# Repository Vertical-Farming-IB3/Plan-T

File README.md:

# Plan-T 🌱  

Plan-T is een vertical farming (VF) project met hydroponics, gericht op het duurzaam kweken van kruiden en groenten. De VF-installatie wordt grotendeels automatisch bestuurd en gemonitord, met ruimte voor menselijke input waar nodig — zoals bij controle, onderhoud en oogst (een vorm van mens-in-de-lus automatisering).

## Voor meer info:  
- [Team Plantenbak](./Plantenbak)  
- [Team Water](./Water)  
- [Team Licht](./Licht)
- [Team Power](./Power)  

Bezoek onze [website](https://vertical-farming-ib3.github.io/),
en zijn [repository](https://github.com/Vertical-Farming-IB3/vertical-farming-ib3.github.io/tree/main).

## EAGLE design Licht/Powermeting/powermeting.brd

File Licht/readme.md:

Het team bestaat uit:
- Daan Vercammen
- Andres Bosman
- Syme Vandenbosch
- Arne Van der Stede
- Cas Truyers
- Stijn Verhaeghe

Meer info [hier](https://vertical-farming-ib3.github.io/Licht/).

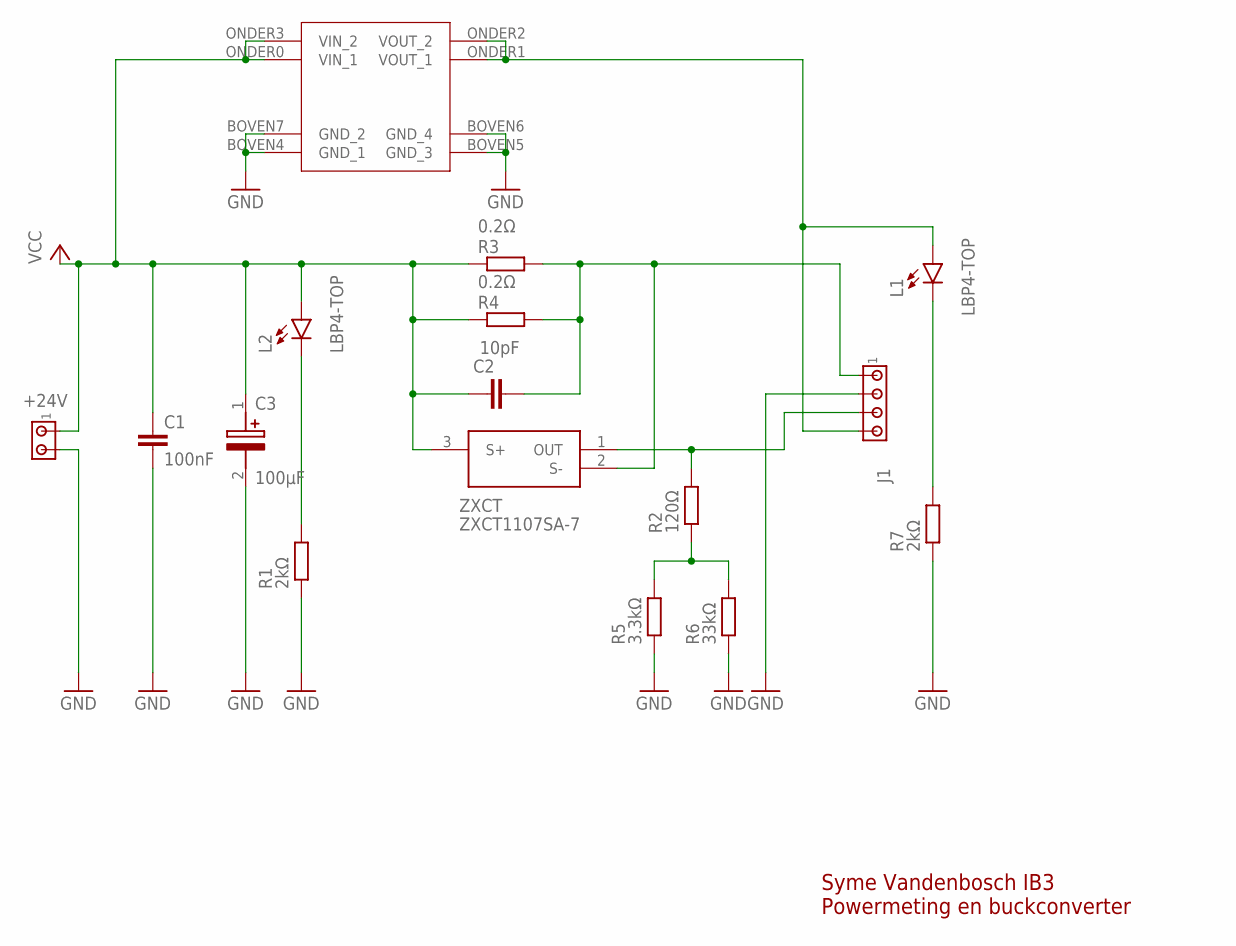
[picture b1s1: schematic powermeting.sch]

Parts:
+24V: MTA02-100; 10X02MTA
C1: 100nF; C0805K
C2: 10pF; C0805K
C3: 100µF; EEHZA1H100R
J1: MTA04-100; 10X04MTA
L1, L2: LBP4-TOP; LED3MM
R1, R7: 2kΩ; M0805
R2: 120Ω; M0805
R3, R4: 0.2Ω; M1206
R5: 3.3kΩ; M0805
R6: 33kΩ; M0805
U$1: BUCK
ZXCT: ZXCT1107SA-7; SOT96P240X110-3N

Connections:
GND: +24V.2, C1.2, C3.2 (-), J1.2, R1.1, R5.1, R6.1, R7.1, U$1.BOVEN4 (GND_1), U$1.BOVEN5 (GND_3), U$1.BOVEN6 (GND_4), U$1.BOVEN7 (GND_2)
unnamed: L1.K (C), R7.2
unnamed: L2.K (C), R1.2
unnamed: R2.1, R5.2, R6.2
unnamed: C2.2, J1.1, R3.1, R4.1, ZXCT.2 (S-)
unnamed: J1.4, L1.A, U$1.ONDER1 (VOUT_1), U$1.ONDER2 (VOUT_2)
unnamed: J1.3, R2.2, ZXCT.1 (OUT)
VCC: +24V.1, C1.1, C2.1, C3.1 (+), L2.A, R3.2, R4.2, U$1.ONDER0 (VIN_1), U$1.ONDER3 (VIN_2), ZXCT.3 (S+)

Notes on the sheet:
Syme Vandenbosch IB3 Powermeting en buckconverter

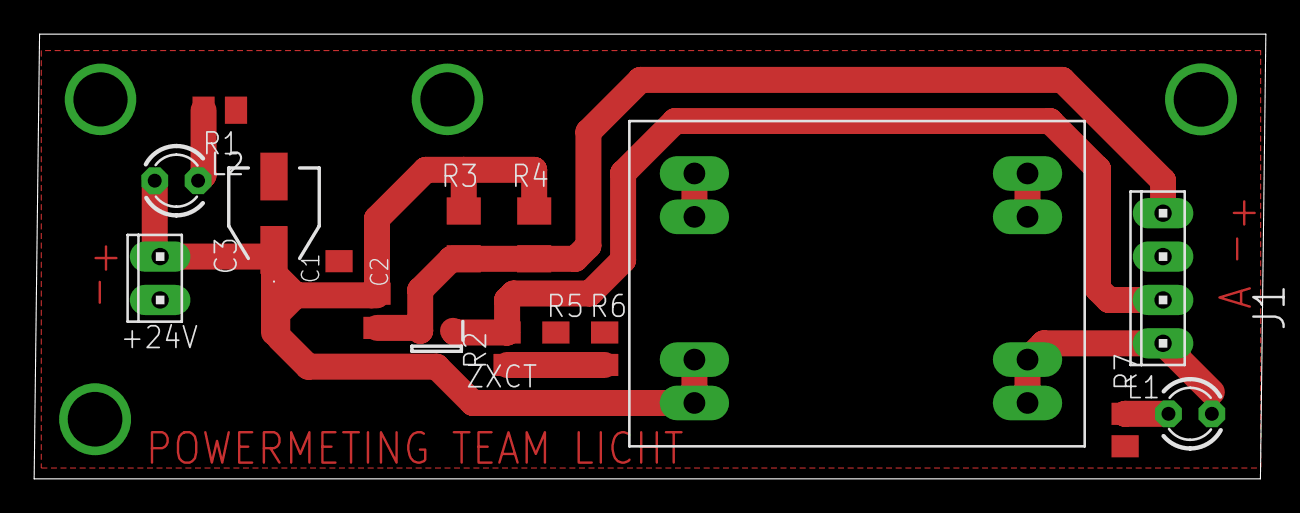
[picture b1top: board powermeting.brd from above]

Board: 2 copper layers, 72.1 x 26.0 mm, 16 parts (0 on the bottom side), 8 nets.

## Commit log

2024-10-16 Brainstorming Session October 16
2024-10-22 added log of 22/10
2024-10-22 Added documentation folder
    Added a doc folder with information about the project done in 2023-2024, specifically the connection of the source to the vertical farm.
2024-12-20 Onderverdeling mappen + markdown watersysteem
    Folders toegevoegd per huidig gekend team + in watersysteem een markdown voorzien met informatie over het watersysteem
2025-01-27 Added 3D-models
    Added 3D-models and assemblies of the water system and common connector (both still WIP)
2025-02-05 Add files via upload
    Enkele opzoekingen. Keuze welke bestellen na controle.
2025-02-06 Log update after presentation
2025-02-06 Overzicht van onderdelen
2025-02-06 UV filter
2025-02-11 Word document samengevoegd met markdown
    Alle informatie uit het word document is in het markdown document geplaatst
2025-02-11 Create test
2025-02-11 Wijzigingen na bespreking
2025-02-11 Update na bespreking
2025-02-17 aanpassing naar keukenmodel
2025-02-18 Update 3D modellen
    Plantenbakken herwerkt (randen weggevijld zodat ze onderaan passen) + Buitenste 'shell' van kast
2025-02-18 PCB requirements input/output
2025-02-18 Ruwe berekening vermogen
2025-02-18 Add files via upload
    Gantt Chart
2025-02-19 PCB Watersysteem initial commit
    Ontwerp PCB initial commit: deel van schema van PCB, custom symbol + footprints (MP1584 buck converter module), symbol+footprint van 5V relais
2025-02-23 Update PCB watersysteem
2025-02-24 PCB update
    ADC verbonden, LED outputs, Eindeloops, Voorbeeld relais
2025-02-24 Moved to correct folder
2025-02-25 Add files via upload
    Vergeten file
2025-02-25 update progress team plantenbak
2025-02-25 Update PCB
    Extra terminals
2025-02-25 Update PCB
    relaisschakelingen verder afgewerkt, endstops afgewerkt, bezig met ultrasone sensors
2025-02-25 Update PCB
    deel footprints geselecteerd, hoogtesensoren ingesteld
2025-02-26 Update PCB
    Footprints LEDs toegevoegd
2025-02-26 Update PCB
    16 bit I2C IO expander toegevoegd (juiste footprint nog na te meten)
2025-02-26 Update PCB
    16 bit IO-expander ingesteld
2025-02-26 PCB update
    Testpunten, relaisschakelingen afgewerkt, adres io expander wijzigbaar, enkele footprints
2025-02-26 Update PCB
    Switch library toegevoegd, IO expander ontkoppel toegevoegd
2025-02-27 Update PCB
    transistoren vervangen door mosfets
2025-02-27 Update PCB
    Footprints toegevoegd
2025-03-01 Update PCB
    IO gemapt, Condensator ADC, Schematic geprint
2025-03-03 Update PCB
    BNC Connectoren ingevoegd, extra footprints
2025-03-04 Update PCB
    alle footprints staan correct, alles in PCB geïmporteert
2025-03-04 Update PCB
    Start met floorplanning
2025-03-04 componenten gegroepeerd
2025-03-04 Indeling gemaakt
2025-03-05 Update PCB
    Placing en routing van vermogen, grootste componenten
2025-03-05 Update PCB
    Alle connecties gemaakt
2025-03-06 Silkscreen
2025-03-06 Afwerking
2025-03-07 ground plane fix
2025-03-08 PCB Design
    PCB Design (nog niet volledig af)
2025-03-08 PCB Update
    samenbrengen designs, polarisaties plaatsen
2025-03-08 Update PCB
    Logotje toegevoegd
2025-03-10 Update PCB
    Afmetingen verkleind (100x100), rerouting, clean-up
2025-03-10 Gewijzigde pins
2025-03-10 Update PCB
    Extra eindwerk rond vias en silkscreen
2025-03-11 Update PCB
    Eindwerk aan PCB (extra vias, meer silkscreen, lichte aanpassing floorplanning,...)
2025-03-11 Update PCB: Gerber Files
    Gerber files met drill holes geplot
2025-03-11 Update PCB
2025-03-11 Update PCB
    M4 -> M3 in Schema
2025-03-11 Pinout toegevoegd
2025-03-11 Website init
2025-03-11 Website test
2025-03-11 Homepage
2025-03-11 disable Jekyll
2025-03-11 disable jekyll
    website stuff
2025-03-11 Generated BOM
2025-03-15 LED pin gewijzigd, I2C toegevoegd
2025-03-15 Update logboek
2025-03-16 Opzoeking voor kalibratie probes
2025-03-18 Update BOM
2025-03-18 Yaml voor watersysteem
2025-03-18 Documentatie vorig jaar
2025-03-18 Create readme.md voor team licht
2025-03-18 files verplaatst
2025-03-18 Create readme.md power
2025-03-18 Current sensor + fixes
    'GPIO' toegevoegd bij pins, update_interval's geplaatst, power sensing toegevoegd
2025-03-28 IBom added
    ibom toegevoegd
2025-04-01 kallibratie stroomsensor
2025-04-01 Create temp
2025-04-01 Create Software
2025-04-01 Kalibratie chemische probes
2025-04-01 add repo icon
2025-04-01 Revert "add repo icon"
    This reverts commit 6380b1b41bed8b2b7aa1ddbbc59e2902adcb05f6.
2025-04-01 Kalibratie selectieve ionen sensoren
2025-04-01 Vermogensmeting
2025-04-02 Weerstandjes gewijzigd voor status LEDs
2025-04-02 betere namen
2025-04-08 hoogtesensoren kallibratie + fixes
2025-04-08 metingen kraantjeswater en voedingsstoffen
2025-04-08 aanpassing concentratie
2025-04-13 Changes for uniformity
2025-04-13 Vertaling
2025-04-13 Eerste grove aanvulling Team water log
2025-04-13 Extra onderverdeling log
2025-04-13 Added to Readme.md log
2025-04-13 Added warning
2025-04-13 Added emojis to keep in theme
2025-04-13 Corrected spelling mistakes
2025-04-20 Kleine aanpassingen
    Kleine aanpassingen logboek en water
2025-04-21 Small corrections (spelling, doubles, ...)
2025-04-22 Update Readme.md
    Logboek 22/04 aangevuld
2025-04-22 Bestellijst
    Nog te vervolledigen
2025-04-22 herkalibratie hoogtesensor
2025-04-22 Beschrijving groep water
2025-04-24 Rename Readme.md to Readme.md
2025-04-24 Rename Gantt Chart.xlsx to Gantt Chart.xlsx
2025-04-24 rename
2025-04-27 pH-waarden
2025-04-27 pH stockoplossing
2025-04-29 Aanpassingen Yaml
    Sensoren gekalibreerd en pH dimensieloos maken.
2025-05-03 tweede kalibratie
2025-05-03 pH kalibratie
2025-05-03 subscript bij grafiekjes
2025-05-03 zelfde schaal
2025-05-06 Vermogen onboard samenvoegen + status
2025-05-06 Update and rename Watersysteem.md to Research.md
    Betere documentatie van research voor gebruik op site.
2025-05-06 Update Research.md
    Klein foutje weg gewerkt.
2025-05-06 dagelijks energieverbruik
2025-05-06 Update Chemische_probes.md
    Toevoegen verwachte waarden water
2025-05-06 Update Research.md
    Kleine aanpassing mixer
2025-05-06 average van stroommeting
2025-05-06 research plantenbak
2025-05-06 Upload BOM
2025-05-06 Fixed mistake in BOM
2025-05-07 uitleg bij watermeting
2025-05-07 LED-PCB export files
2025-05-08 Update README.md plantenvak
2025-05-09 Create directory
2025-05-09 Added driver schematics and PCB
2025-05-09 geen pH sturen wanneer het pompje aanligt
2025-05-12 filters op sensoren
2025-05-12 Oude log vervangen door planning
2025-05-12 wijziging filter pH
2025-05-12 3D-print pH-houder
2025-05-12 3D print hoogtesensor
2025-05-12 3D-print chemische probes
2025-05-13 Upload presentation
2025-05-13 Added/moved files
2025-05-13 Add files via upload
    powermeting toevoeging pcb
2025-05-17 .docx to md
2025-05-20 Changed filenames
2025-05-21 Added video
2025-05-21 Small changes
